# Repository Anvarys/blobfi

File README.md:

<div align="center">
  
</div>

<h2 align="center">Blobfi</h2>
<p align="center">
A custom PCB-based Tamagotchi virtual pet called Blobfi
</p>

## About the project

A custom PCB-based Tamagotchi-like virtual pet built the XIAO-ESP32-C6 MCU, featuring a 0.96" OLED display, 500mah battery with USB-C charging (via the esp32), 3 buttons, a temperature sensor and a vibration motor.

I made this project to have my own custom tamagotchi pet called Blobfi, which is a blobfish, because I love blobfishes!!

I used [Tanishq's tamagotchi](https://github.com/TaniWanKenobi/tamagotchi/) as insiration & reference.

## How to build your own Blobfi

To build this project yourself, first you need to 3d print the top and bottom parts ([link to the folder with 3d models](https://github.com/Anvarys/blobfi/tree/master/CAD)), also you preferably should print 4 of the screen supports that will be used to mount hold the screen parallel to the PCB. Then you need to buy all the [parts](https://github.com/Anvarys/blobfi/blob/master/BOM.csv) and the [PCB](https://github.com/Anvarys/blobfi/blob/master/blobfi_gerber.zip) and then assemple it all together as shown on the picture below (also you need to screw the PCB and the top to the bottom enclosure in using 3 M3x8mm screws each):

And then you need to flash the ESP32 using my [blobfi_firmware](https://github.com/Anvarys/blobfi/tree/master/blobfi_firmware) sketch in Arduino IDE, also you need to install Adafruit SSD1306, OneWireNg, DallasTemperature libraries with their dependencies.

## Tools I used

For PCB & schematic design I used [KiCAD](https://kicad.org), for 3D design I used [Autodesk Fusion](https://www.autodesk.com/products/fusion-360/overview) (free version), for coding the firmware I used [Arduino IDE](https://www.arduino.cc/en/software/), for testing the firmware I used [Wowki](https://wokwi.com/) hardware simulator and for general design (Edge.Cuts & the Zine) I used [Figma](https://figma.com)

## PCB design

## Schematic

## 3D model

## Firmware

Blobfi has 3 stats which decrease by 1 each 5 minutes:
- Hunger
- Happiness
- Energy

And if the temperature of Blobfi goes above 40C or below 5C happiness will decrease at 2x rate.

Depending on these stats you will have a different image of a blobfish on your main screen, here is an example of a happy Blobfi:

Emulated render:

An actual photo:

If any of the stats will go below 0 it will be set to 0 and the vibration motor will shake your Blobfi as it wants to eat/sleep/play.

Also if any stat is below 10 then the bar will blink on the screen.

Actions buttons do:
- Left button: Feed Blobfi, +15 hunger and +5 energy
- Middle button: Play with Blobfi, +15 happiness and -5 energy
- Right button: Put Blobfi to sleep, +15 energy
- Left and right buttons at the same time: Put the device into deep sleep (basically turning it off, you can wake it up by pressing any button)

And here is an example of an action animation (duration - 3s):

#### Deep sleep

Also my firmware uses ESP32 deep sleep feature, which allows it to go into a very low power use mode. After 30 seconds of inactivity (not pressing any buttons) the device will go into deep sleep.

When the device goes into deep sleep it will disable the display, but it will start an internal timer for the next update of Blobfi (5 minutes minus the time from the last update that had already passed) and it will still listen to any button inputs, and if you press any button it will wake up to the normal state.

This allows to reduce ESP32C6 and display's total current from about **50mA** to about **17µA** which is around **2941 times less current**. This allows for the device to actually work for longer than some 10-15 hours, now it can do multiple weeks (theoretically months, has not tested that in practice yet).

## BOM

|Name                     |Price (Total)|Link                                                |
|-------------------------|-------------|----------------------------------------------------|
|Lithium battery 500mah   |US$6.73      |https://fr.aliexpress.com/item/1005009540712263.html|
|XIAO ESP32 C6            |US$6.71      |https://fr.aliexpress.com/item/1005006987272421.html|
|M3 8mm screws            |US$3.55      |https://fr.aliexpress.com/item/1005010597960014.html|
|Aliexpress shipping      |US$5.10      |-                                                   |
|JLCPCB PCB               |US$2.00      |https://jlcpcb.com                                  |
|JLCPCB shipping & customs|US$2.20      |-                                                   |
|4K7 Resistor             |US$0.58      |https://www.lcsc.com/product-detail/C119339.html    |
|MY18B20L temp sensor     |US$1.94      |https://www.lcsc.com/product-detail/C5259249.html   |
|0.96'' OLED display      |US$2.25      |https://www.lcsc.com/product-detail/C5248080.html   |
|Tactile button           |US$0.54      |https://www.lcsc.com/product-detail/C2888493.html   |
|Vibration motor          |US$0.52      |https://www.lcsc.com/product-detail/C2759982.html   |
|Male pin headers (20pcs) |US$0.60      |https://www.lcsc.com/product-detail/C49261205.html  |
|2N2222A transistor       |US$0.90      |https://www.lcsc.com/product-detail/C5330385.html   |
|0.1uF capacitor          |US$0.61      |https://www.lcsc.com/product-detail/C5632427.html   |
|LCSC shipping & handling |US$12.57     |-                                                   |
|                         |             |                                                    |
|Total                    |US$46.80     |                                                    |

The display is out of stock so the price is for buying one from "Other suppliers" on LCSC

## Build photos

For reference the squares are 5x5mm

[_demo_](https://www.youtube.com/shorts/axdSh3g87GE)

## My zine for this project

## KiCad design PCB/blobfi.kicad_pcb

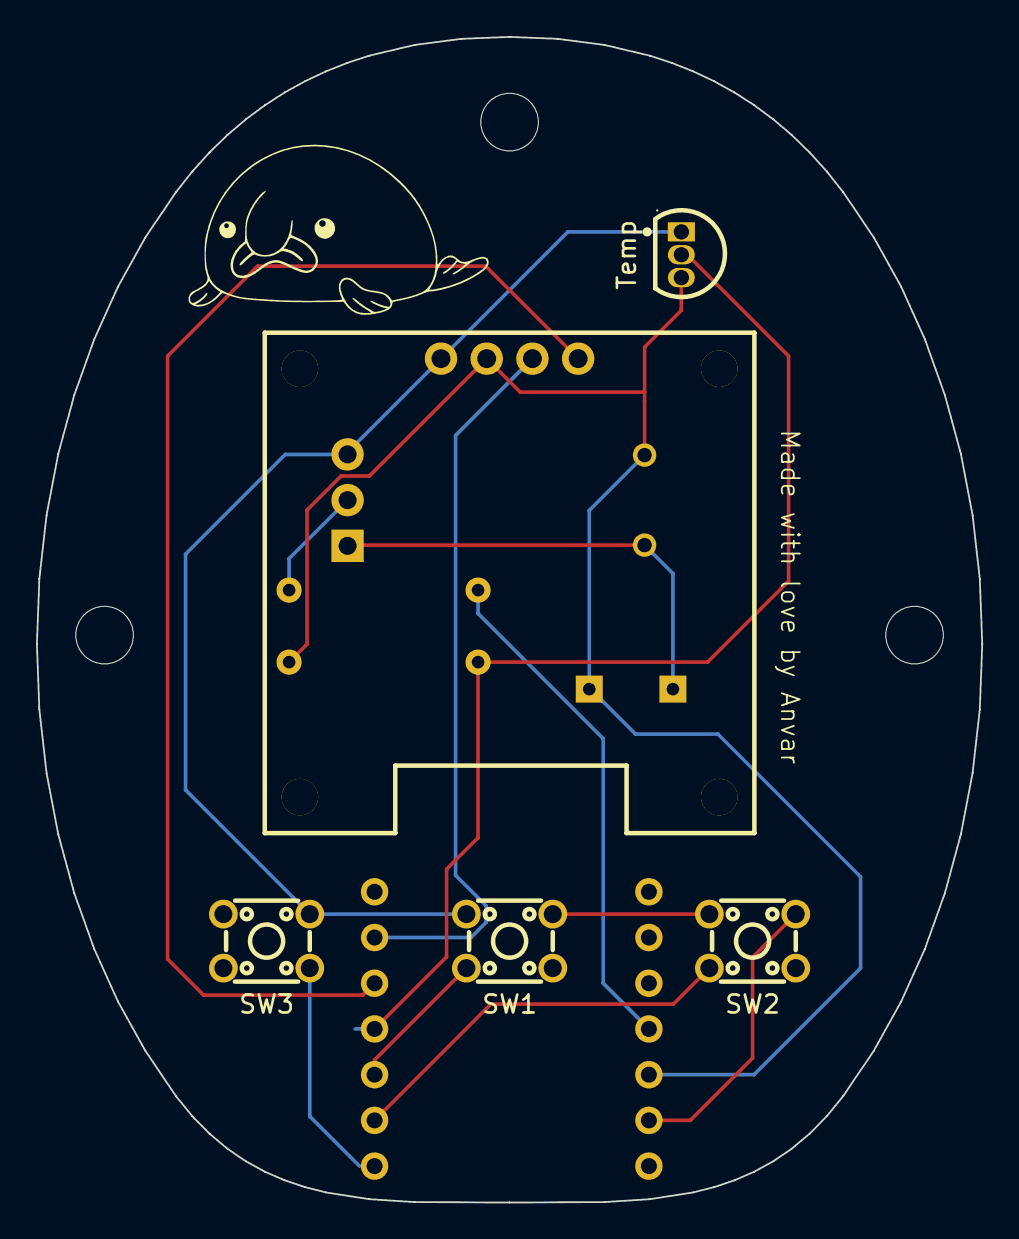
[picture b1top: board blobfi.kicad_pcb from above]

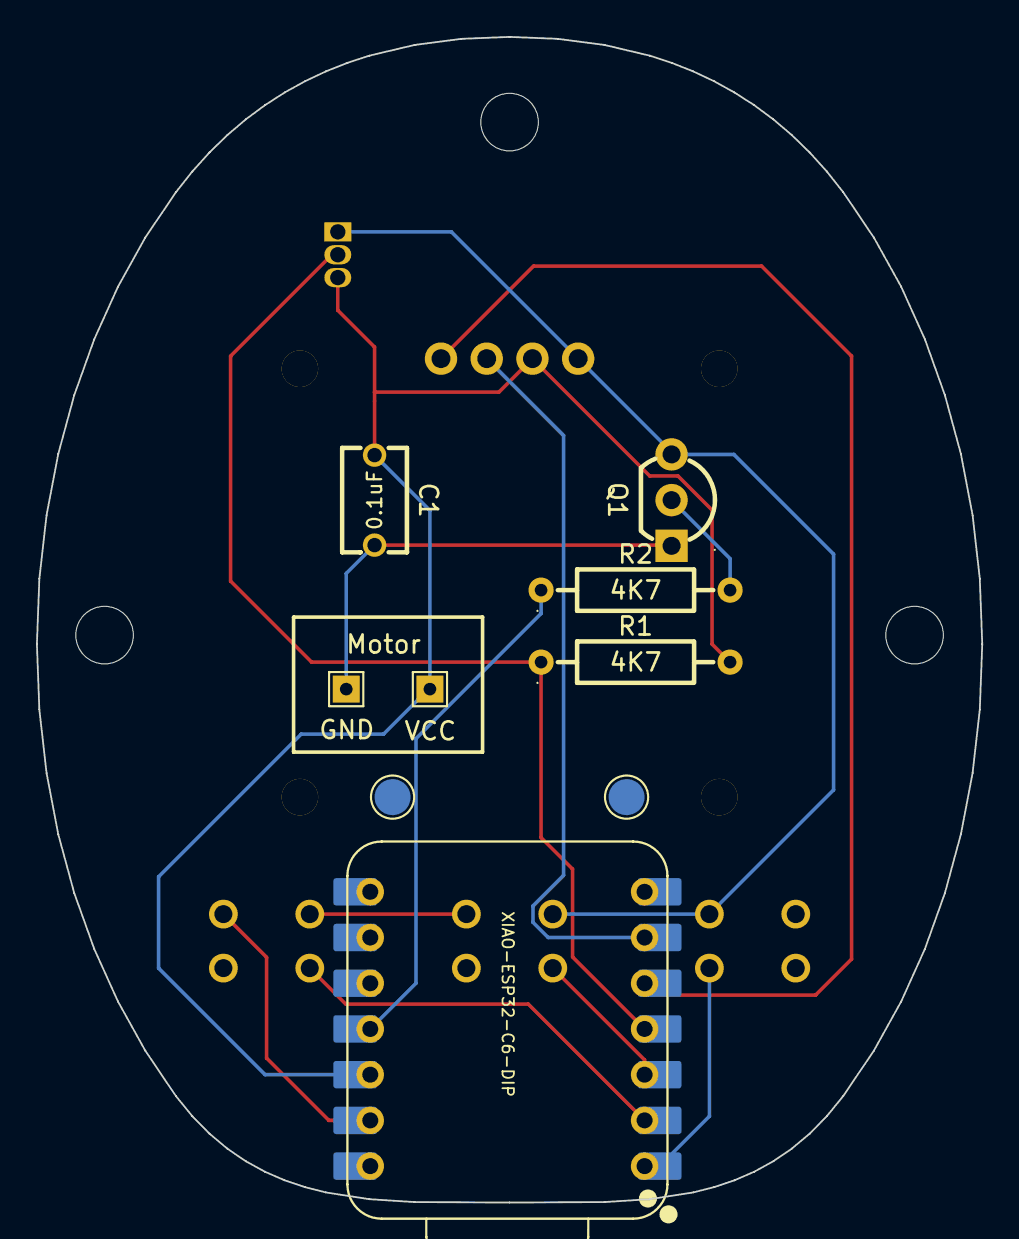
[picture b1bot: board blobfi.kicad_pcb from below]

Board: 2 copper layers, 52.5 x 64.8 mm, 14 parts (9 on the bottom side), 11 nets.

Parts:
C1: 100nF; CAP-TH_L5.8-W3.6-P5.0-D0.6
GND: Motor GND; TestPoint_THTPad_1.5x1.5mm_Drill0.7mm
Q1: 2N2222A; TO-92-3_L4.8-W3.7-P2.54-R
R1, R2: 4.7KΩ; RES-TH_BD2.3-L6.5-P10.50-D0.5
SW1, SW2, SW3: SW_Push; SW-TH_4P-L4.5-W4.5-P3.00-LS4.8
TP1: VBAT-SMD; TestPoint_Pad_D2.0mm
TP2: GND-SMD; TestPoint_Pad_D2.0mm
Temp: MY18B20L; TO-92-3_L4.8-W3.7-P1.27-L
U1: XIAO-ESP32-C6-DIP
U2: HS96L03W2C03; OLED-TH_L27.8-W27.2-P2.54_C9900033791
VCC: Motor VCC; TestPoint_THTPad_1.5x1.5mm_Drill0.7mm

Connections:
+3V3: C1.2, R1.2, Temp.3 (VDD), U1.12 (3V3), U2.2 (VCC), VCC.1 (1_1)
GND: Q1.3 (E), SW1.1, SW2.1, SW3.1, Temp.1 (GND), U1.13 (GND), U2.1 (GND)
unnamed: Q1.2 (B), R2.2
unnamed: C1.1, GND.1 (1_1), Q1.1 (C)
unnamed: SW3.2, U1.1 (GPIO0_A0_D0)
unnamed: SW2.2, U1.2 (GPIO1_A1_D1)
unnamed: SW1.2, U1.3 (GPIO2_A2_D2)
unnamed: R2.1, U1.11 (GPIO18_D10_MOSI)
unnamed: R1.1, Temp.2 (DQ), U1.4 (GPIO21_D3)
unnamed: U1.5 (GPIO22_D4_SDA), U2.4 (SDA)
unnamed: U1.6 (GPIO23_D5_SCL), U2.3 (SCL)

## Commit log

2026-04-06 fix: removed unused .history
2026-04-06 created basic firmware
2026-04-06 fixed a lot of firmware bugs
2026-04-06 added images
2026-04-06 added 3d models
2026-04-06 created README
2026-04-06 added a zine for this project
2026-04-06 modified zine to have a title next to the qr-code
2026-04-06 added "By Anvar" to the zine
2026-04-22 modify README
2026-04-22 add proper warning
2026-04-22 created new firmware with deep sleep
2026-04-24 added temp sensor & vibration motor & time persistance after deep sleep
2026-04-24 update BOM
2026-04-24 update PCB & remove old firmware
2026-04-24 update CAD files
2026-04-25 update README and little changes in firmware & BOM
2026-04-25 updated images
2026-04-25 update the zine
2026-04-26 update BOM & 3d model with new battery
2026-04-26 update firmware
2026-04-26 update BOM note
2026-04-26 remove useless Qty column in BOM
2026-04-26 remove unused note column in BOM
2026-04-26 update zine
2026-04-26 add assembly
2026-05-08 removed fake coupon by jlcpcb from the BOM
2026-05-22 disable temp sensor & minor firmware improvements
2026-05-26 fixed temp sensor, now working
2026-05-28 little CAD changes
2026-06-01 updated with irl photos
2026-06-11 added demo video
